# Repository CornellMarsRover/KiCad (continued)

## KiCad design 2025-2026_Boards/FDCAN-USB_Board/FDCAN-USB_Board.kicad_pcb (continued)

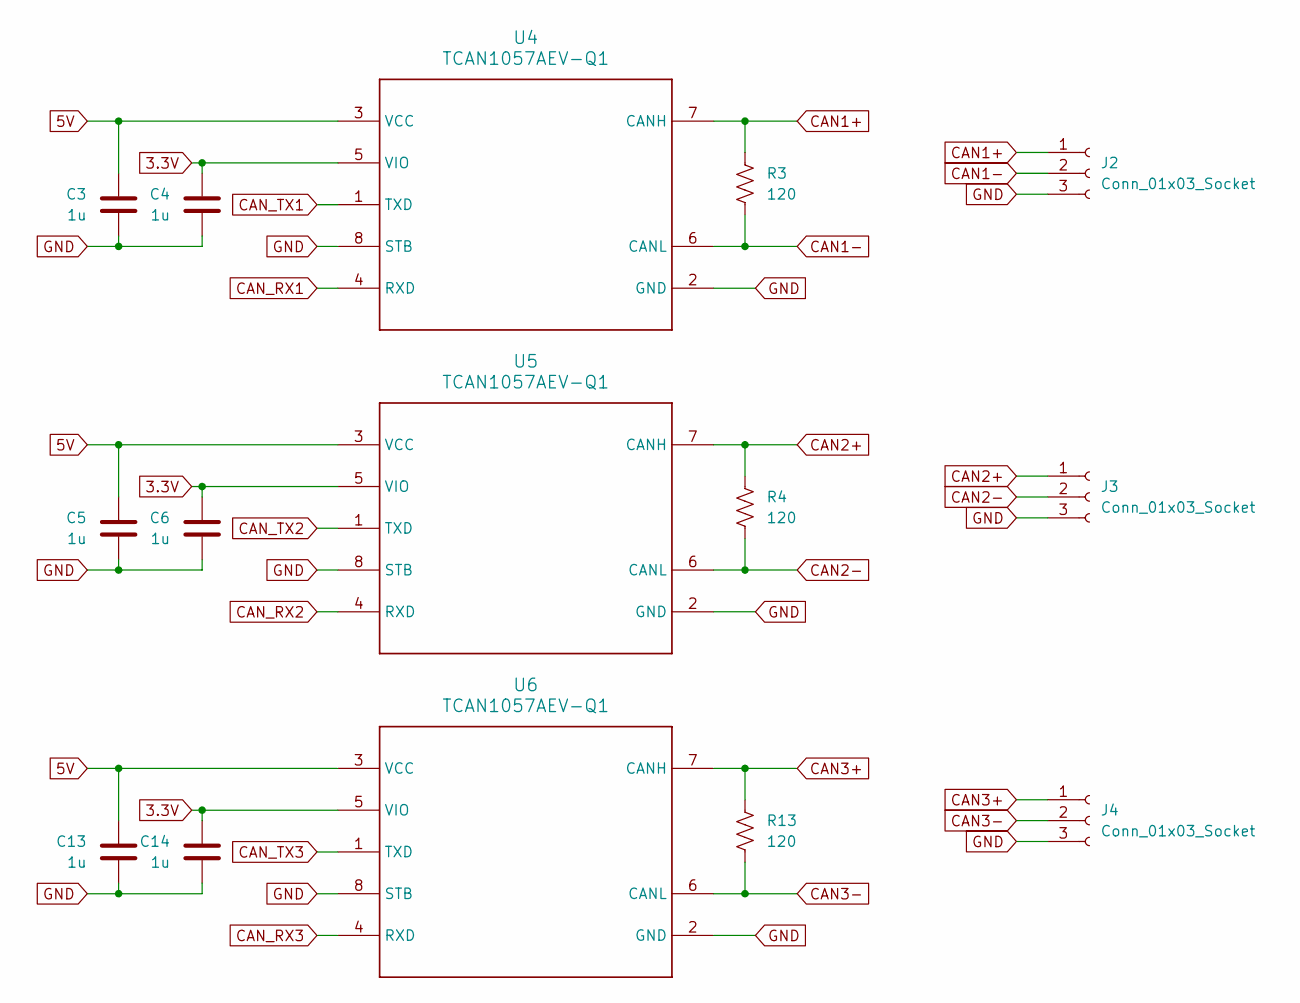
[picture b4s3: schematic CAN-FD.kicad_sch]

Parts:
C3, C4, C5, C6, C13, C14: 1u; C_0402_1005Metric
J2, J3, J4: Conn_01x03_Socket; JST_PH_S3B-PH-SM4-TB_1x03-1MP_P2.00mm_Horizontal
R3, R4, R13: 120; R_1206_3216Metric; MPN RC1206FR-07110RL
U4, U5, U6: TCAN1057AEV-Q1; SOIC-8_3.9x4.9mm_P1.27mm; MPN TCAN1057AEVDRQ1

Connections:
3.3V: C4.1, C6.1, C14.1, U4.5 (VIO), U5.5 (VIO), U6.5 (VIO); also elsewhere on the board
5V: C3.1, C5.1, C13.1, U4.3 (VCC), U5.3 (VCC), U6.3 (VCC); also elsewhere on the board
CAN1+: J2.1, R3.1, U4.7 (CANH)
CAN1-: J2.2, R3.2, U4.6 (CANL)
CAN2+: J3.1, R4.1, U5.7 (CANH)
CAN2-: J3.2, R4.2, U5.6 (CANL)
CAN3+: J4.1, R13.1, U6.7 (CANH)
CAN3-: J4.2, R13.2, U6.6 (CANL)
CAN_RX1: U4.4 (RXD); also elsewhere on the board
CAN_RX2: U5.4 (RXD); also elsewhere on the board
CAN_RX3: U6.4 (RXD); also elsewhere on the board
CAN_TX1: U4.1 (TXD); also elsewhere on the board
CAN_TX2: U5.1 (TXD); also elsewhere on the board
CAN_TX3: U6.1 (TXD); also elsewhere on the board
GND: C3.2, C4.2, C5.2, C6.2, C13.2, C14.2, J2.3, J3.3, J4.3, U4.2 (GND), U4.8 (STB), U5.2 (GND), U5.8 (STB), U6.2 (GND), U6.8 (STB); also elsewhere on the board

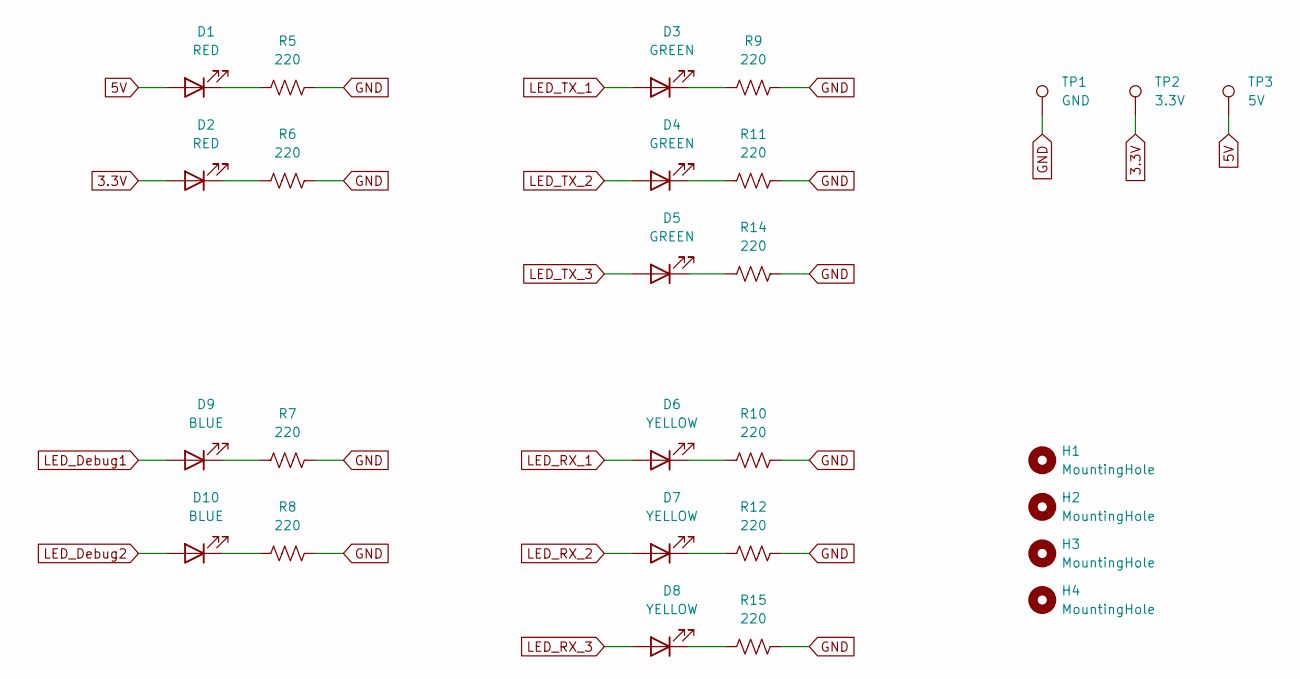
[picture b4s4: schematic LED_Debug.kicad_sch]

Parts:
D1, D2: RED; LED_0603_1608Metric
D3, D4, D5: GREEN; LED_0603_1608Metric
D6, D7, D8: YELLOW; LED_0603_1608Metric
D9, D10: BLUE; LED_0603_1608Metric
H1, H2, H3, H4: MountingHole; MountingHole_2.7mm_M2.5
R5, R6, R7, R8, R9, R10, R11, R12, R14, R15: 220; R_0402_1005Metric
TP1: GND; TestPoint_Pad_D1.0mm
TP2: 3.3V; TestPoint_Pad_D1.0mm
TP3: 5V; TestPoint_Pad_D1.0mm

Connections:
3.3V: D2.2 (A), TP2.1; also elsewhere on the board
5V: D1.2 (A), TP3.1; also elsewhere on the board
GND: R5.2, R6.2, R7.2, R8.2, R9.2, R10.2, R11.2, R12.2, R14.2, R15.2, TP1.1; also elsewhere on the board
LED_Debug1: D9.2 (A); also elsewhere on the board
LED_Debug2: D10.2 (A); also elsewhere on the board
LED_RX_1: D6.2 (A); also elsewhere on the board
LED_RX_2: D7.2 (A); also elsewhere on the board
LED_RX_3: D8.2 (A); also elsewhere on the board
LED_TX_1: D3.2 (A); also elsewhere on the board
LED_TX_2: D4.2 (A); also elsewhere on the board
LED_TX_3: D5.2 (A); also elsewhere on the board
unnamed: D1.1 (K), R5.1
unnamed: D2.1 (K), R6.1
unnamed: D3.1 (K), R9.1
unnamed: D4.1 (K), R11.1
unnamed: D5.1 (K), R14.1
unnamed: D6.1 (K), R10.1
unnamed: D7.1 (K), R12.1
unnamed: D8.1 (K), R15.1
unnamed: D9.1 (K), R7.1
unnamed: D10.1 (K), R8.1

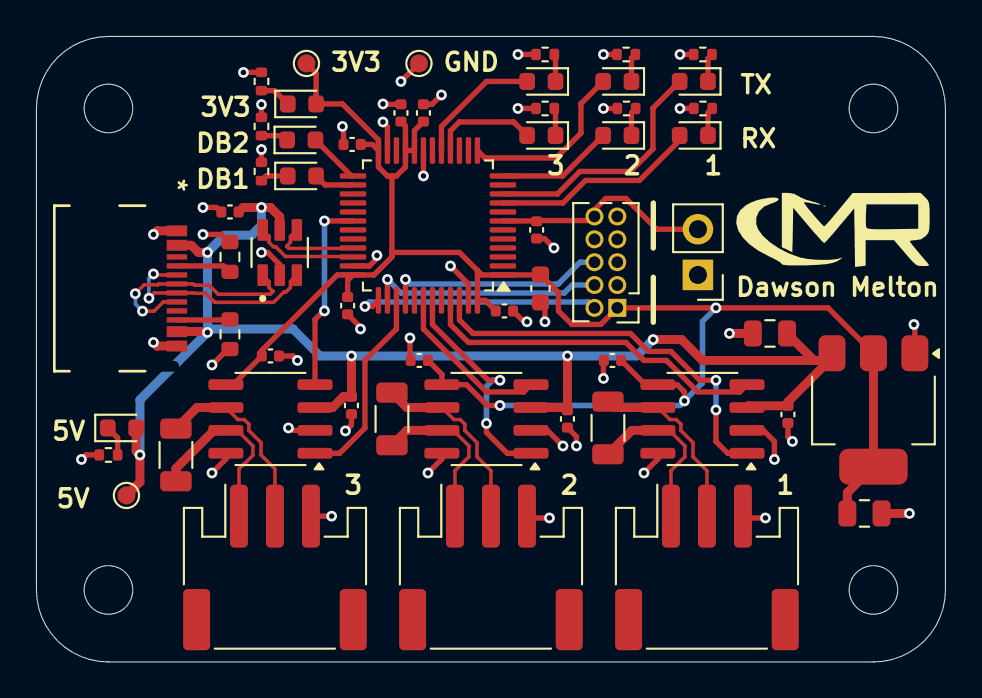
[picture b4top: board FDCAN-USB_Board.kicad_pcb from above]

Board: 2 copper layers, 50.5 x 34.8 mm, 60 parts (0 on the bottom side), 43 nets.

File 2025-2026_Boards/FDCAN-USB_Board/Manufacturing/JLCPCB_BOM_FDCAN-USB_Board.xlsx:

Comment | Designator | Footprint | JLCPCB Part #
10uF, 25V | C1 | Capacitor_SMD:C_0805_2012Metric | C15850
22uF, 25V | C2 | Capacitor_SMD:C_0805_2012Metric | C45783
1uF, 25V | C3,C4,C5,C6,C11,C12,C13,C14 | Capacitor_SMD:C_0402_1005Metric | C52923
100nF, 25V | C7,C8,C9,C15,C16 | Capacitor_SMD:C_0402_1005Metric | C100072
4.7uF, 25V | C10 | Capacitor_SMD:C_0603_1608Metric | C69335
Red, Lite-On LTST-C193KRKT-5A | D1,D2 | LED_SMD:LED_0603_1608Metric | C157741
Yellow, Lite-On LTST-C193KSKT-5A | D3,D4,D5 | LED_SMD:LED_0603_1608Metric | C160477
Green, Lite-On LTST-C193KGKT-5A | D6,D7,D8 | LED_SMD:LED_0603_1608Metric | C125102
Blue, Lite-On LTST-C193TBKT-5A | D9,D10 | LED_SMD:LED_0603_1608Metric | C125103
JST S3B-PH-SM4-TB | J2,J3,J4 | JST_PH_S3B-PH-SM4-TB_1x03-1MP_P2.00mm_Horizontal | C265101
61300211121, Wurth Elektronik | J5 | PinHeader_1x02_P2.54mm_Vertical | C2915055
HX PZ1.27-2x5P ZZ, hanxia | J6 | PinHeader_2x05_P1.27mm_Vertical | C22438120
2171790001, Molex | J7 | 2171790001_MOL | C3197684
5.1k, YAGEO RC0603FR-075K1L | R1,R2 | Resistor_SMD:R_0603_1608Metric | C105580
120, YAGEO RC1206FR-07120RL | R3,R4,R13 | Resistor_SMD:R_1206_3216Metric | C114928
220, YAGEO RC0402FR-07220RL | R5,R6,R7,R8,R9,R10,R11,R12,R14,R15 | Resistor_SMD:R_0402_1005Metric | C112291
AMS1117-3.3 | U1 | SMD:SOT-223-3_TabPin2 | C347222
USBLC6-2SC6 | U2 | SOT95P280X145-6N | C7519
STM32G474CET6 | U3 | LQFP-48_7x7mm_P0.5mm | C730125
TCAN1057AEVDRQ1 | U4,U5,U6 | SOIC-8_3.9x4.9mm_P1.27mm | C3234997

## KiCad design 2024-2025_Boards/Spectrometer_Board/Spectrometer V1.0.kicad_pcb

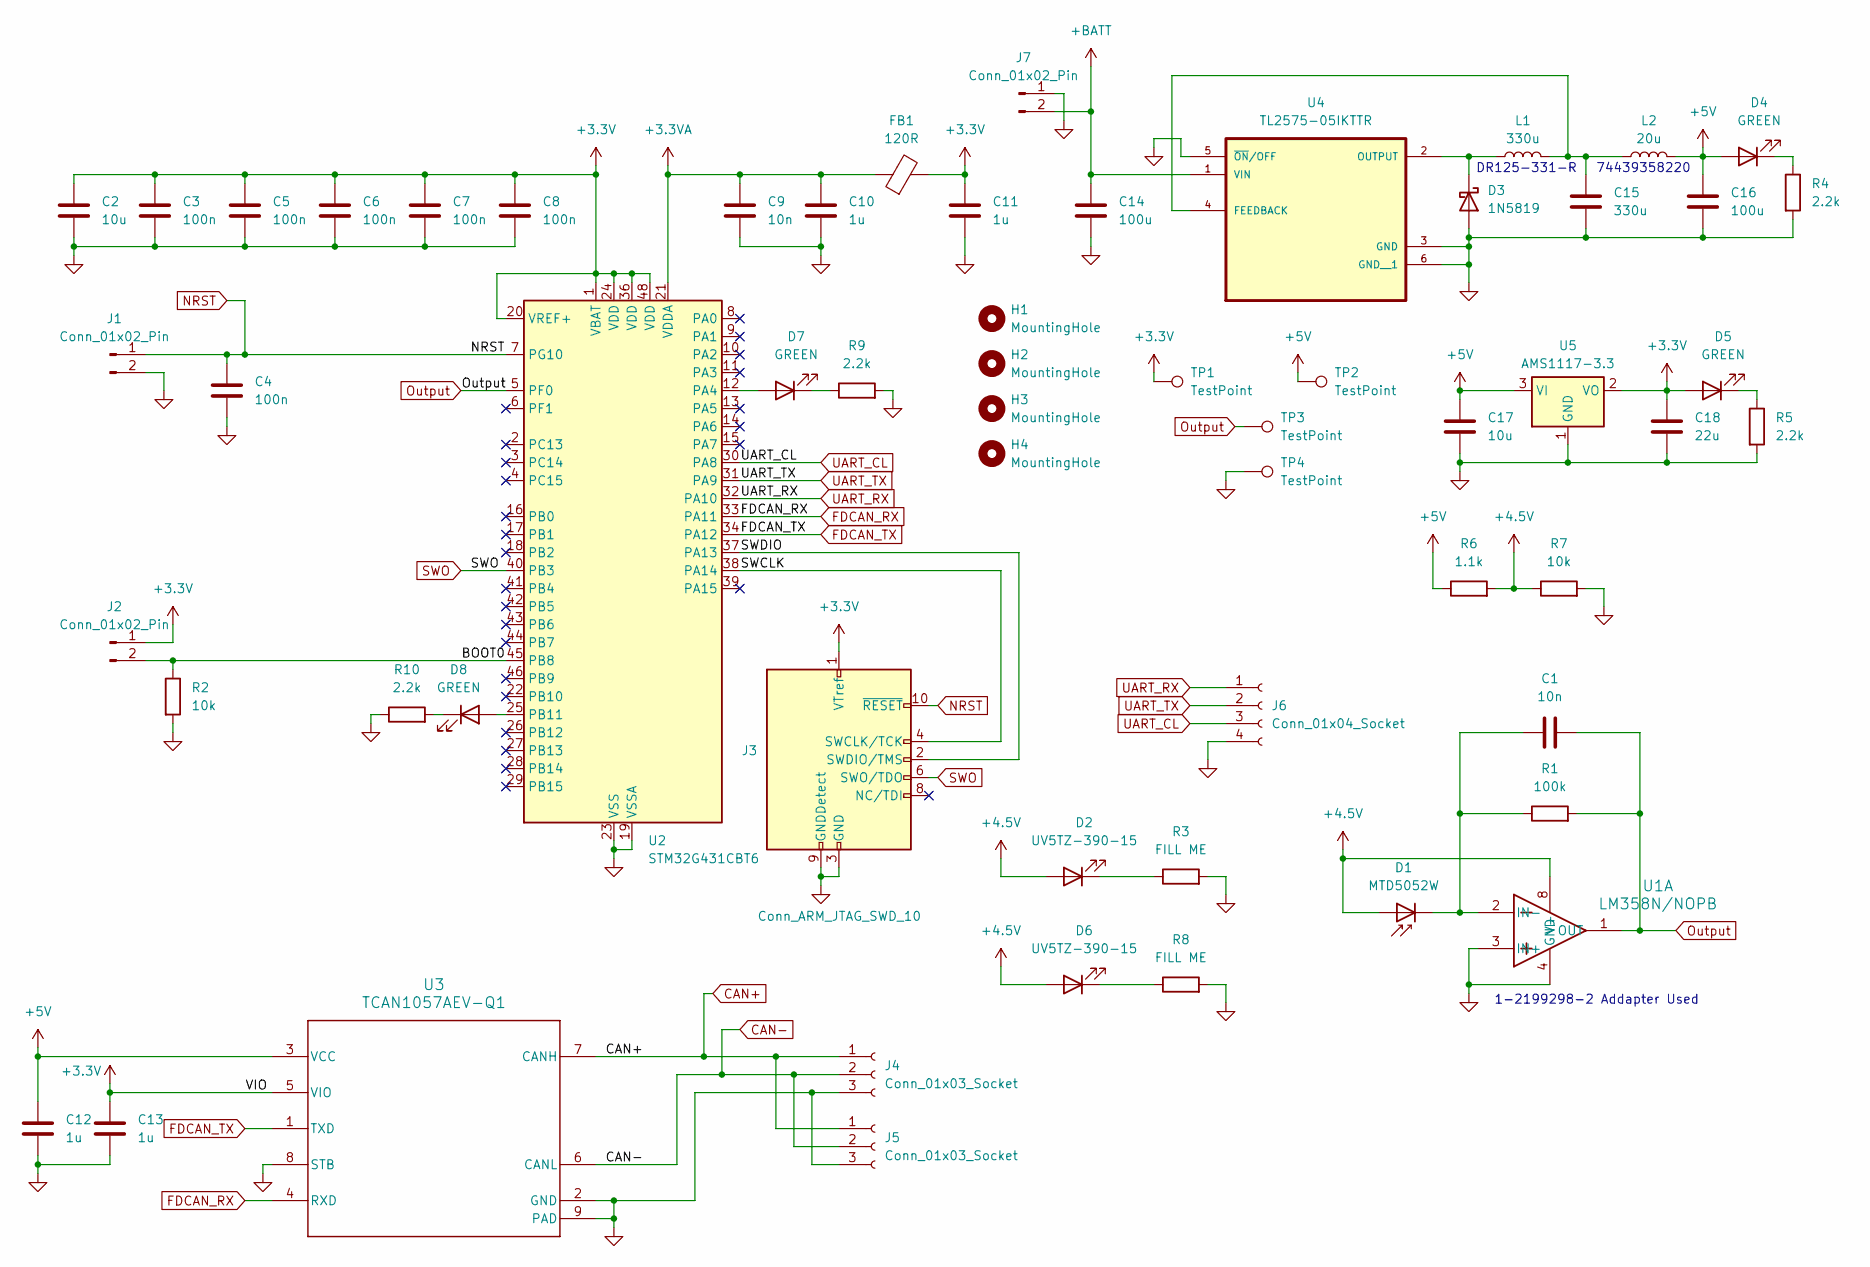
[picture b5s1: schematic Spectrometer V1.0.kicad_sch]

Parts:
C1: 10n; C_Rect_L4.0mm_W2.5mm_P2.50mm
C2: 10u; C_0603_1608Metric
C3, C4, C5, C6, C7, C8: 100n; C_0402_1005Metric
C9: 10n; C_0402_1005Metric
C10, C11, C12, C13: 1u; C_0402_1005Metric
C14: 100u; C_Radial_D8.0mm_H11.5mm_P3.50mm
C15: 330u; C_1210_3225Metric
C16: 100u; C_0805_2012Metric
C17: 10u; C_0805_2012Metric
C18: 22u; C_0805_2012Metric
D1: MTD5052W; LED_D5.0mm
D2, D6: UV5TZ-390-15; LED_D5.0mm
D3: 1N5819; D_DO-41_SOD81_P7.62mm_Horizontal
D4, D5, D7, D8: GREEN; LED_0603_1608Metric
FB1: 120R; L_0603_1608Metric
H1, H2, H3, H4: MountingHole; MountingHole_3.2mm_M3
J1, J2: Conn_01x02_Pin; PinHeader_1x02_P2.54mm_Vertical
J3: Conn_ARM_JTAG_SWD_10; PinHeader_2x05_P1.27mm_Vertical
J4, J5: Conn_01x03_Socket; JST_PH_S3B-PH-SM4-TB_1x03-1MP_P2.00mm_Horizontal
J6: Conn_01x04_Socket; JST_ZE_S04B-ZESK-2D_1x04_P1.50mm_Horizontal
J7: Conn_01x02_Pin; AMASS_XT30PW-M_1x02_P2.50mm_Horizontal
L1: 330u; DR125
L2: 20u; WE-XHMI_8080
R1: 100k; R_Axial_DIN0204_L3.6mm_D1.6mm_P7.62mm_Horizontal
R2: 10k; R_0402_1005Metric
R3, R8: FILL ME; R_Axial_DIN0204_L3.6mm_D1.6mm_P7.62mm_Horizontal
R4, R5, R9, R10: 2.2k; R_0402_1005Metric
R6: 1.1k; R_Axial_DIN0204_L3.6mm_D1.6mm_P7.62mm_Horizontal
R7: 10k; R_Axial_DIN0204_L3.6mm_D1.6mm_P7.62mm_Horizontal
TP1, TP2, TP3, TP4: TestPoint; TestPoint_Pad_D1.0mm
U1: LM358N/NOPB; CONN8_1-2199298-2_TEC
U2: STM32G431CBT6; LQFP-48_7x7mm_P0.5mm
U3: TCAN1057AEV-Q1; SOIC-8_3.9x4.9mm_P1.27mm; MPN TCAN1057AEVDRQ1
U4: TL2575-05IKTTR; TO-263-5_TabPin6
U5: AMS1117-3.3; SOT-223-3_TabPin2

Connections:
+3.3V: C2.1, C3.1, C5.1, C6.1, C7.1, C8.1, C11.1, C13.1, C18.1, D5.2 (A), FB1.2, J2.1, J3.1 (VTref), TP1.1, U2.1 (VBAT), U2.20 (VREF+), U2.24 (VDD), U2.36 (VDD), U2.48 (VDD), U3.5 (VIO), U5.2 (VO)
+3.3VA: C9.1, C10.1, FB1.1, U2.21 (VDDA)
+4.5V: D1.2 (A), D2.2 (A), D6.2 (A), R6.2, R7.1, U1.8 (V+)
+5V: C12.1, C16.1, C17.1, D4.2 (A), L2.2, R6.1, TP2.1, U3.3 (VCC), U5.3 (VI)
+BATT: C14.1, J7.2, U4.1 (VIN)
/BOOT0: J2.2, R2.1, U2.45 (PB8)
/SWCLK: J3.4 (SWCLK/TCK), U2.38 (PA14)
/SWDIO: J3.2 (SWDIO/TMS), U2.37 (PA13)
CAN+: J4.1, J5.1, U3.7 (CANH)
CAN-: J4.2, J5.2, U3.6 (CANL)
FDCAN_RX: U2.33 (PA11), U3.4 (RXD)
FDCAN_TX: U2.34 (PA12), U3.1 (TXD)
GND: C2.2, C3.2, C4.2, C5.2, C6.2, C7.2, C8.2, C9.2, C10.2, C11.2, C12.2, C13.2, C14.2, C15.2, C16.2, C17.2, C18.2, D3.2 (A), J1.2, J3.3 (GND), J3.5 (GND), J3.9 (GNDDetect), J4.3, J5.3, J6.4, J7.1, R2.2, R3.2, R4.2, R5.2, R7.2, R8.2, R9.2, R10.1, TP4.1, U1.3 (IN+), U1.4 (GND), U2.19 (VSSA), U2.23 (VSS), U2.35 (VSS), U2.47 (VSS), U3.2 (GND), U3.8 (STB), U3.9 (PAD), U4.3 (GND), U4.5 (~ON/OFF), U4.6 (GND__1), U5.1 (GND)
NRST: C4.1, J1.1, J3.10 (~RESET), U2.7 (PG10)
unnamed: C1.1, D1.1 (K), R1.1, U1.2 (IN-)
unnamed: D2.1 (K), R3.1
unnamed: D3.1 (K), L1.1, U4.2 (OUTPUT)
unnamed: D4.1 (K), R4.1
unnamed: D5.1 (K), R5.1
unnamed: D6.1 (K), R8.1
unnamed: D7.2 (A), U2.12 (PA4)
unnamed: D7.1 (K), R9.1
unnamed: D8.2 (A), U2.25 (PB11)
unnamed: D8.1 (K), R10.2
unnamed: C15.1, L1.2, L2.1, U4.4 (FEEDBACK)
Output: C1.2, R1.2, TP3.1, U1.1 (OUT), U2.5 (PF0)
SWO: J3.6 (SWO/TDO), U2.40 (PB3)
UART_CL: J6.3, U2.30 (PA8)
UART_RX: J6.1, U2.32 (PA10)
UART_TX: J6.2, U2.31 (PA9)

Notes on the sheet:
DR125-331-R
74439358220
1-2199298-2 Addapter Used

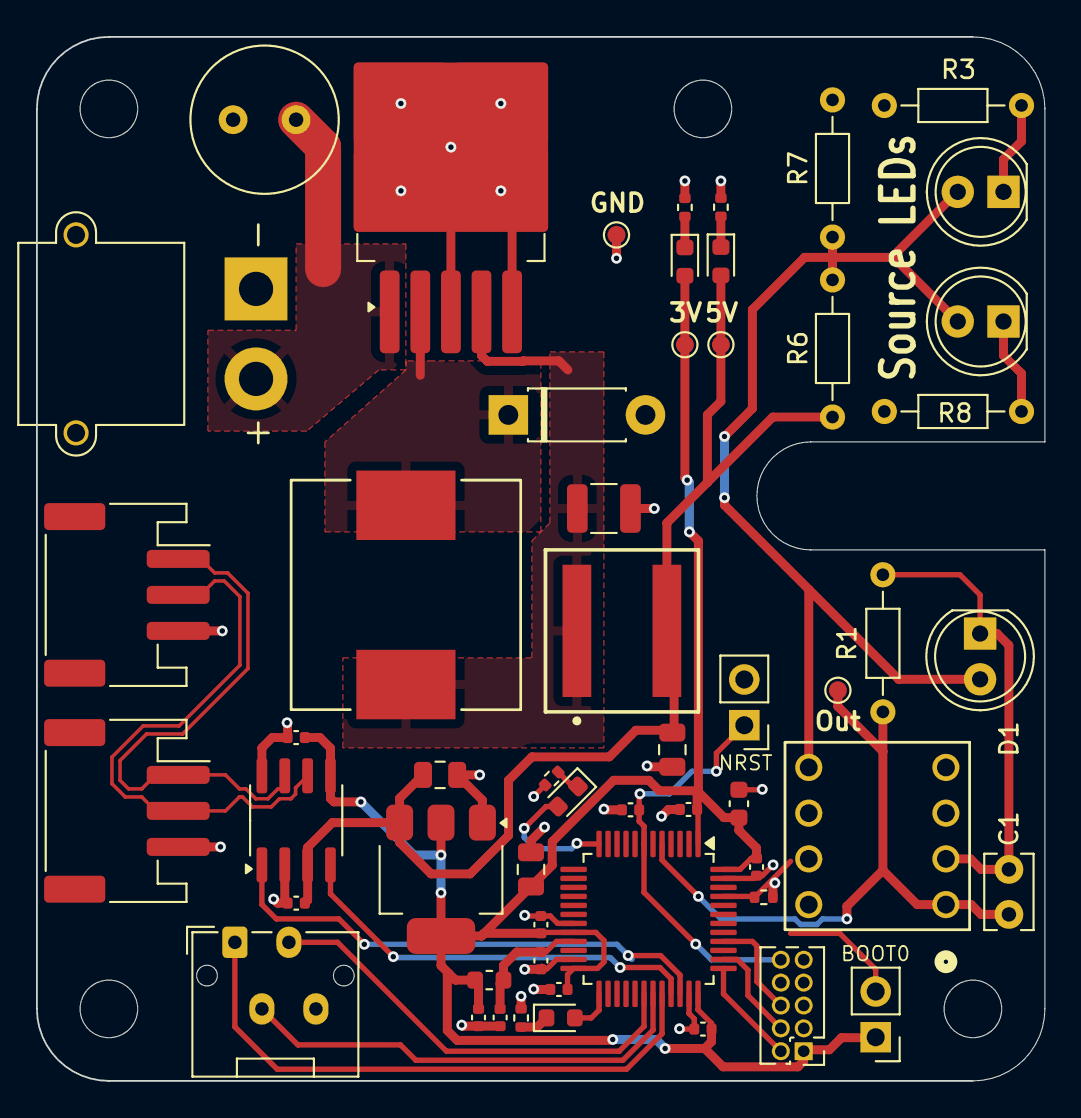
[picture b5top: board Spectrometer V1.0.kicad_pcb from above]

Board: 2 copper layers, 56.0 x 58.0 mm, 59 parts (0 on the bottom side), 30 nets.

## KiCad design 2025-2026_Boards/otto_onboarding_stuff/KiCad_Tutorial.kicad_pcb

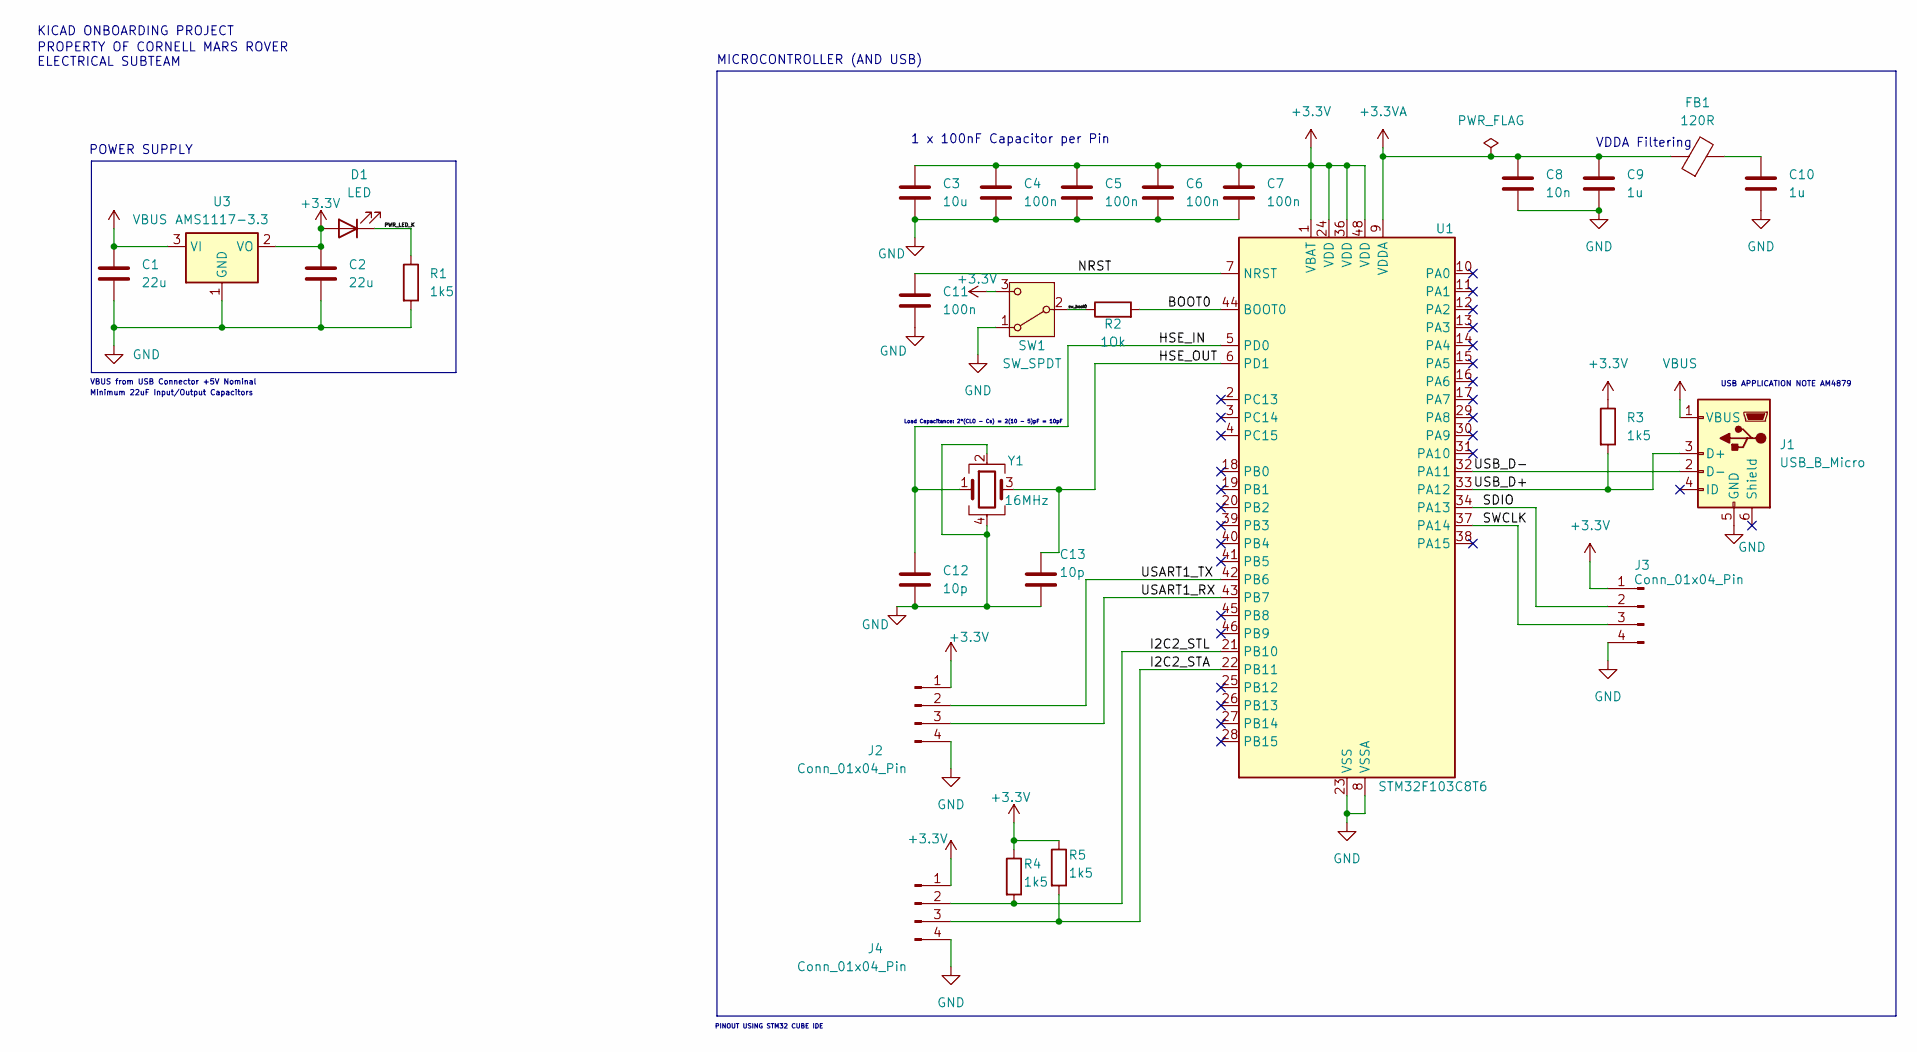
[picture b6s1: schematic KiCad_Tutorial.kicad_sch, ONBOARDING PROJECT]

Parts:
C1, C2: 22u; C_0805_2012Metric
C3: 10u; C_0201_0603Metric
C4, C5, C6, C7, C11: 100n; C_0402_1005Metric
C8: 10n; C_0402_1005Metric
C9, C10: 1u; C_0402_1005Metric
C12, C13: 10p; C_0402_1005Metric
D1: LED; C_0201_0603Metric
FB1: 120R; LED_0603_1608Metric
J1: USB_B_Micro; USB_Micro-B_Wuerth_629105150521
J2, J3, J4: Conn_01x04_Pin; PinHeader_1x04_P2.54mm_Vertical
R1, R3, R4, R5: 1k5; R_0402_1005Metric
R2: 1Ok; R_0402_1005Metric
SW1: SW_SPDT; SW_Lever_1P2T_NKK_GW12LxH
U1: STM32F103C8T6; LQFP-48_7x7mm_P0.5mm
U3: AMS1117-3.3; SOT-223-3_TabPin2
Y1: 16MHz; Crystal_SMD_3225-4Pin_3.2x2.5mm

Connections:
+3.3V: C2.1, C3.1, C4.1, C5.1, C6.1, C7.1, D1.2 (A), J2.1, J3.1, J4.1, R3.1, R4.1, R5.1, SW1.3 (C), U1.1 (VBAT), U1.24 (VDD), U1.36 (VDD), U1.48 (VDD), U3.2 (VO)
+3.3VA: C8.1, C9.1, FB1.1, U1.9 (VDDA)
/BOOT0: R2.2, U1.44 (BOOT0)
/HSE_IN: C12.1, U1.5 (PD0), Y1.1
/HSE_OUT: C13.1, U1.6 (PD1), Y1.3
/I2C2_STA: J4.3, R5.2, U1.22 (PB11)
/I2C2_STL: J4.2, R4.2, U1.21 (PB10)
/NRST: C11.1, U1.7 (NRST)
/PWR_LED_K: D1.1 (K), R1.1
/SDIO: J3.2, U1.34 (PA13)
/SWCLK: J3.3, U1.37 (PA14)
/USART1_RX: J2.3, U1.43 (PB7)
/USART1_TX: J2.2, U1.42 (PB6)
/USB_D+: J1.3 (D+), R3.2, U1.33 (PA12)
/USB_D-: J1.2 (D-), U1.32 (PA11)
/sw_boot0: R2.1, SW1.2 (B)
GND: C1.2, C2.2, C3.2, C4.2, C5.2, C6.2, C7.2, C8.2, C9.2, C10.2, C11.2, C12.2, C13.2, J1.5 (GND), J2.4, J3.4, J4.4, R1.2, SW1.1 (A), U1.8 (VSSA), U1.23 (VSS), U1.35 (VSS), U1.47 (VSS), U3.1 (GND), Y1.2, Y1.4
unnamed: C10.1, FB1.2
VBUS: C1.1, J1.1 (VBUS), U3.3 (VI)

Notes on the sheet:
KICAD ONBOARDING PROJECT
Load Capacitance: 2*(CLO - Cs) = 2(10 - 5)pF = 10pF
Minimum 22uF Input/Output Capacitors
VBUS from USB Connector +5V Nominal
POWER SUPPLY
1 x 100nF Capacitor per Pin
MICROCONTROLLER (AND USB)
USB APPLICATION NOTE AM4879
PINOUT USING STM32 CUBE IDE
PROPERTY OF CORNELL MARS ROVER ELECTRICAL SUBTEAM
VDDA Filtering

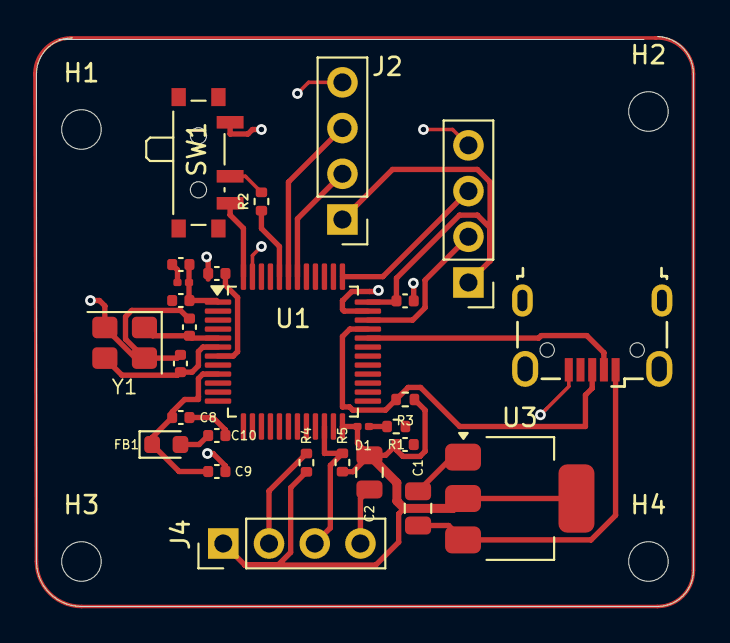
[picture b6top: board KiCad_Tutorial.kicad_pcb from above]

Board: 2 copper layers, 36.5 x 31.7 mm, 32 parts (0 on the bottom side), 19 nets.

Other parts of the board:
H1, H2, H3, H4: MountingHole; MountingHole_2.2mm_M2

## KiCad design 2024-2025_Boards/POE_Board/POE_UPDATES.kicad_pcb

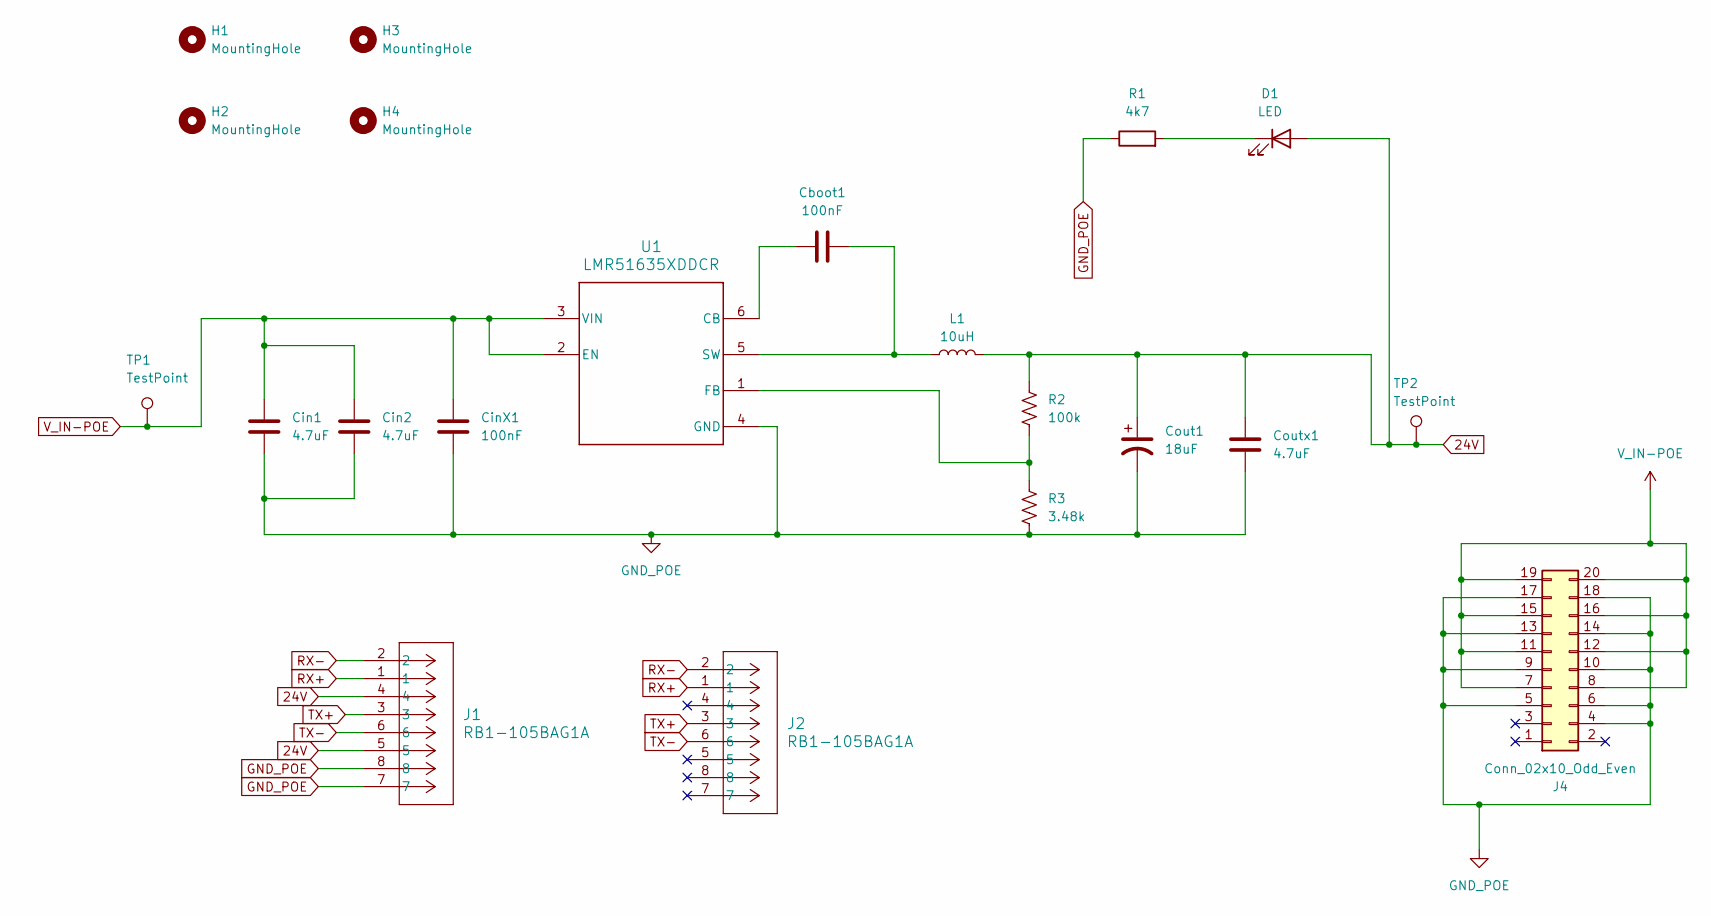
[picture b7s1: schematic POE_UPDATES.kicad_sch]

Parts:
Cboot1: 100nF; C_0402_1005Metric
Cin1, Cin2: 4.7uF; C_1206_3216Metric
CinX1: 100nF; C_0603_1608Metric
Cout1: 18uF; CP_Elec_8x6.9
Coutx1: 4.7uF; C_1206_3216Metric
D1: LED; LED_0603_1608Metric_Pad1.05x0.95mm_HandSolder
H1, H2, H3, H4: MountingHole; MountingHole_3.2mm_M3
J1, J2: RB1-105BAG1A; CONN8_5BAG1A_WIZ
J4: Conn_02x10_Odd_Even; CONN20_D10-RA-BK_SUL
L1: 10uH; IND_BOURNS_SDR1806
R1: 4k7; R_0402_1005Metric_Pad0.72x0.64mm_HandSolder
R2: 100k; R_0402_1005Metric
R3: 3.48k; R_0402_1005Metric
TP1, TP2: TestPoint; TestPoint_Pad_D1.0mm
U1: LMR51635XDDCR; DDC0006A-MFG

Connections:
24V: Cout1.1, Coutx1.1, D1.2 (A), J1.4, J1.5, L1.2, R2.1, TP2.1
GND_POE: Cin1.2, Cin2.2, CinX1.2, Cout1.2, Coutx1.2, J1.7, J1.8, J4.4, J4.5, J4.6, J4.9, J4.10, J4.13, J4.14, J4.17, J4.18, R1.1, R3.2, U1.4 (GND)
unnamed: D1.1 (K), R1.2
unnamed: Cboot1.1, U1.6 (CB)
unnamed: R2.2, R3.1, U1.1 (FB)
unnamed: Cboot1.2, L1.1, U1.5 (SW)
RX+: J1.1, J2.1
RX-: J1.2, J2.2
TX+: J1.3, J2.3
TX-: J1.6, J2.6
V_IN-POE: Cin1.1, Cin2.1, CinX1.1, J4.7, J4.8, J4.11, J4.12, J4.15, J4.16, J4.19, J4.20, TP1.1, U1.2 (EN), U1.3 (VIN)

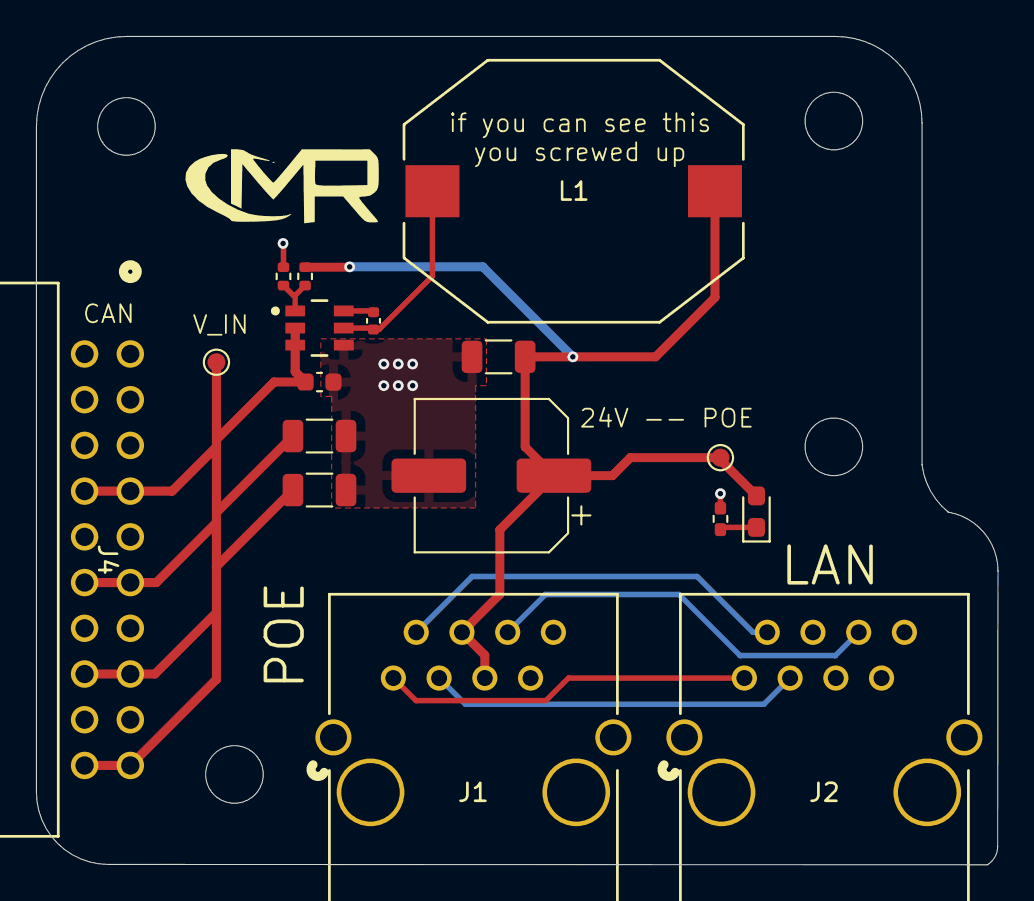
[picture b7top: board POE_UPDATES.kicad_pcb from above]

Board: 2 copper layers, 53.4 x 46.0 mm, 21 parts (0 on the bottom side), 11 nets.
